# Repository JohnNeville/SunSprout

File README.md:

# SunSprout

> [!WARNING]
> **Prototype hardware: charging works, validation is incomplete.** A first hub was built and
> tested from commit [`1645733`](https://github.com/JohnNeville/SunSprout/commit/1645733).
> Charging, charge termination and running from the battery alone worked on it, and testing also
> found issues. The current design files fix them, but that revision has **not been built yet**,
> and not every feature has been bench-tested. [Testing status](https://johnneville.github.io/SunSprout/docs/testing-status)
> lists each feature. You can build the tested prototype with its known issues, or the current
> design with its untested fixes. The commit history shows what changed.
>
> **Before you connect a battery:**
> - **Set the cell chemistry in the firmware first.** The charger comes up for a 4.2 V cell by
>   default. The firmware sets the charge limit from `cell_chemistry` (LiFePO4 charges to 3.65 V),
>   so set it to match your cell.
> - **Fit a 10 kΩ NTC thermistor** on the battery, or set `ts_ignore: true` (turns temperature
>   protection off). Otherwise the charger won't charge.
> - **Set the charge current in the firmware to suit your pack, and never above 2000 mA.** The
>   hardware input-current limit only restricts it loosely, so the firmware ceiling is what holds it.
> - **Check polarity.** The reverse-polarity protection was changed after the prototype and the
>   new design is untested on hardware.
>
> A wrongly configured charger can damage a lithium cell. Build one board and bring it up on USB
> power with no battery before ordering a batch.
>
> Feedback is welcome, especially on the power path, the charger and fuel-gauge configuration, and
> anything in [docs/hub/modules/](docs/hub/modules/) where the reasoning looks wrong.

An open-hardware solar and battery powered sensor system. SunSprout covers both halves of a
deployment: the **hub**, a custom board that manages power and talks to the network, and the
**remote sensors** that connect back to it over a long cable run.

The hub is the custom hardware in this project. The remote sensors are largely assembled from
existing modules, and are documented here so that a whole system can be reproduced rather than
inferred.

## The hub

A compact power-management and connectivity board built around the **ESP32-C5**. It takes power
from USB-C, a small DC or solar source, or a lithium battery. It charges the battery, regulates
a 3.3 V system rail, and exposes two independent I2C buses — one for its own power-management
ICs, and one for sensors, buffered onto a differential pair so it can drive a long cable.

| | |
|---|---|
| Documentation site | **[johnneville.github.io/SunSprout](https://johnneville.github.io/SunSprout/)** — pinout, connectors, power behaviour |
| Build one | [Order from JLCPCB](website/docs/fabrication/ordering-jlcpcb.md) and [Getting started](website/docs/getting-started.md) — fabrication settings, assembly checks, first flash |
| Design files | [hardware/hub/](hardware/hub/) — KiCad 10 project, hand-routed |
| Why it is built this way | [docs/hub/modules/](docs/hub/modules/) — per-IC design notes |
| Firmware | [SunSprout-firmware](https://github.com/JohnNeville/SunSprout-firmware) — ESPHome configuration; [docs/hub/firmware.md](docs/hub/firmware.md) for the reasoning |
| Off-board parts you need | [docs/hub/extra-components.md](docs/hub/extra-components.md) |

Every IC's datasheet-required external components are drawn directly into the schematic rather
than treated as black-box breakout modules. The schematic and PCB are maintained by hand in
KiCad; there is no generator producing them.

### Design decisions worth knowing up front

- **Two independent I2C buses.** An always-on internal bus carries the charger and the fuel
  gauge. A separate switched bus feeds the differential buffer that drives the two 8P8C jacks,
  plus its own STEMMA QT connector. A fault on a long external cable cannot stall the bus that
  reports the battery state.
- **Protection sized to what each port is for.** ESD/TVS on the ports meant to carry a cable
  off-board — the differential I2C lines on the 8P8C jacks, the USB-C data lines, and the USB
  `VBUS` rail. The STEMMA QT ports, GPIO headers and thermistor inputs have none, by design:
  they are for sensors inside the same enclosure. Reverse-polarity protection guards the
  battery and solar inputs, each sized to that input's real voltage range; USB-C gets none,
  being a keyed, spec-defined connector that cannot be connected backwards.
- **Alert lines go to their own GPIOs.** The charger and the fuel gauge each get a dedicated
  interrupt pin, so firmware reacts to a fault without polling, and without interrogating both
  devices to find which one raised it.
- **Connector families differ by role on purpose.** The battery and solar inputs use physically
  different connectors, so a solar source cannot be plugged into the battery input. The two
  thermistor inputs are a third family again, chosen to be field-terminable rather than
  requiring a pre-terminated probe.

## Remote sensors

A custom board, `SunSproutSatellite` ([hardware/satellite/](hardware/satellite/)), is the
differential-I2C endpoint that sits at the plant end of the cable — it terminates the line,
converts back to standard I2C, and reads four capacitive soil-moisture probes plus one
1-Wire soil-temperature probe. It integrates what was previously an off-the-shelf SparkFun
QwiicBus EndPoint wired to a breadboarded ADS1115. See
[docs/satellite/modules/](docs/satellite/modules/) for the per-IC design notes, and
[Use Cases](https://johnneville.github.io/SunSprout/use-cases) for the deployed topology.

**Status: schematic-capture spec only** — the KiCad project is scaffolded but no board has
been fabricated yet.

## Repository layout

```
.
├── hardware/
│   ├── hub/                  # the hub's KiCad project, libraries, and SPICE decks
│   └── satellite/            # the satellite's KiCad project and libraries
├── firmware/                 # ESPHome configuration for the hub
├── docs/
│   ├── hub/
│   │   ├── modules/          # per-IC design notes: part choice, passive values, constraints
│   │   ├── firmware.md       # why the firmware is configured the way it is
│   │   └── extra-components.md
│   └── satellite/
│       └── modules/          # per-IC design notes for the satellite board
├── tools/                    # Dockerised KiCad CLI: validation, fab outputs, doc assets
└── website/                  # Docusaurus documentation site
```

## Documentation

The prose documentation is split by audience:

- **[docs/hub/modules/](docs/hub/modules/)** explains *why* the hub is built the way it is —
  why each part was chosen, and why its passives have the values and packages they do. Written
  for someone reading the design cold. Start at the [index](docs/hub/modules/README.md).
- **[docs/hub/firmware.md](docs/hub/firmware.md)** explains the firmware decisions — why the
  watchdog is off, why the charge voltage comes from the declared chemistry, and what the
  `SFET_PRESENT` bit unlocks. The configuration itself is in [SunSprout-firmware](https://github.com/JohnNeville/SunSprout-firmware); the chip
  drivers live in [esphome-bq-drivers](https://github.com/JohnNeville/esphome-bq-drivers).
- **[website/](website/)** is the source for the user-facing documentation site, published at
  **[johnneville.github.io/SunSprout](https://johnneville.github.io/SunSprout/)**: pinout,
  connectors, power behaviour, and downloads.

Manufacturer datasheets are deliberately not redistributed here. Each design note names the
exact part number, so you can get the datasheet from the manufacturer.

## Building and validating

Docker is the only prerequisite. No local KiCad installation is required.

```bash
tools/run_kicad_validation.sh
```

```bash
tools/generate-docs-assets.sh
```

The first runs ERC and DRC. The second regenerates the board renders, schematic PDF, STEP
model, interactive BOM, and pinout diagram under `website/static/`. Re-run it after any
schematic or layout change, so that the published assets never go stale.

See [hardware/hub/README.md](hardware/hub/README.md) for what you can do with the KiCad project
without any extra setup, and which external libraries are optional.

## License

Copyright John Neville 2026.
This source describes Open Hardware and is licensed under the CERN-OHL-S v2.

You may redistribute and modify this source and make products using it
under the terms of the CERN-OHL-S v2 (https://ohwr.org/cern_ohl_s_v2.txt).

This source is distributed WITHOUT ANY EXPRESS OR IMPLIED WARRANTY,
INCLUDING OF MERCHANTABILITY, SATISFACTORY QUALITY AND FITNESS FOR A
PARTICULAR PURPOSE. Please see the CERN-OHL-S v2 for applicable conditions.

Source location: https://github.com/JohnNeville/SunSprout

See [LICENSE](LICENSE) for the full license text.

This design also vendors Espressif's official CC BY-SA 4.0 KiCad library for the ESP32-C5
module. See [NOTICE.md](NOTICE.md) for that credit and an acknowledgment of other technical
references consulted during design.

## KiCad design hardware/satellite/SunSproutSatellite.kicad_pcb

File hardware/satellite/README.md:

# SunSproutSatellite — KiCad project

The satellite board's KiCad 10 project. Open `SunSproutSatellite.kicad_pro`.

This board is a differential-I2C endpoint: it terminates the far end of the cable coming
from a [SunSproutHub](../hub/), converts the differential pair back to standard I2C, and
reads four capacitive soil-moisture probes plus one 1-Wire soil-temperature probe. For the
design reasoning behind each part, see [docs/satellite/modules/](../../docs/satellite/modules/).

**Status: Complete 4-layer PCB layout.** The project schematic and PCB layout are fully completed, featuring a 4-layer stackup (JLC04161H-7628), controlled-impedance differential I2C routing, dedicated inner reference planes (`In1.Cu` and `In2.Cu`), ESD protection, cable power decoupling, and complete DFM rule verification with 0 DRC violations.

## Layout & Architecture

| Path | Contents |
|---|---|
| `SunSproutSatellite.kicad_sch` | Root hierarchical schematic |
| `sheets/i2c_endpoint_v1.kicad_sch` | Differential I2C endpoint, PCA9615 buffer, termination array, cable power entry, power status LED (LED1), cut jumper (JP19), and headers J1, J7, J8, J9 |
| `sheets/adc_sensors_v1.kicad_sch` | ADS1115 16-bit 4-channel ADC, JST PH moisture probe headers (J2–J5), and address jumper JP1 |
| `sheets/onewire_v1.kicad_sch` | DS2482S-100+ I2C to 1-Wire bridge, JST PH probe header (J6), and bit-weighted address jumper JP16 |
| `SunSproutSatellite.kicad_pcb` | Completed 4-layer PCB layout (27.25 mm × 51.10 mm) with inner ground/power planes |
| `SunSproutSatellite.kicad_dru` | Custom JLCPCB 4-layer design rules (clearances, trace widths, track angles, and annular rings) |
| `../libraries/` | Project-specific symbol & footprint library (shared with Hub) |

## External library dependencies

Two parts have no stock KiCad equivalent and are copied in from the hub's own libraries
rather than referenced externally:

| Part | Symbol | Footprint |
|---|---|---|
| PCA9615 differential I2C buffer | `project:PCA9615DPZ` | `Snapeda:TSSOP10_SOT552-1_NXP-L` |
| 8P8C/RJ45 jack | `project:RJHSE5380_QwiicBusCompatible` | `Snapeda:AMPHENOL_RJHSE5380` |

Both footprints resolve externally via `KICAD_3RD_PARTY` the same way the hub's do (see
[hardware/hub/README.md](../hub/README.md#external-library-dependencies)) — or, simpler for
a board with only two such parts: place each once, then use KiCad's "Update PCB from
Schematic" so the footprint geometry gets embedded directly into this project's own files,
exactly as the hub does for every part once placed. After that, no external dependency
remains for either part.

Every other part on this board — the ADS1115 ADC, the DS2482 1-Wire bridge, the ESD
protection diode array, and all connectors — resolves from KiCad's own stock libraries with
zero setup.

## Regenerating the documentation assets

Documentation assets (3D board renders, interactive BOM, and interactive pinout SVGs) are generated via `tools/generate-docs-assets.sh`. The generated assets live under `website/static/` and `website/static/img/`. Release assets (schematic PDFs, STEP models, and fabrication zips) are produced by the release workflow.

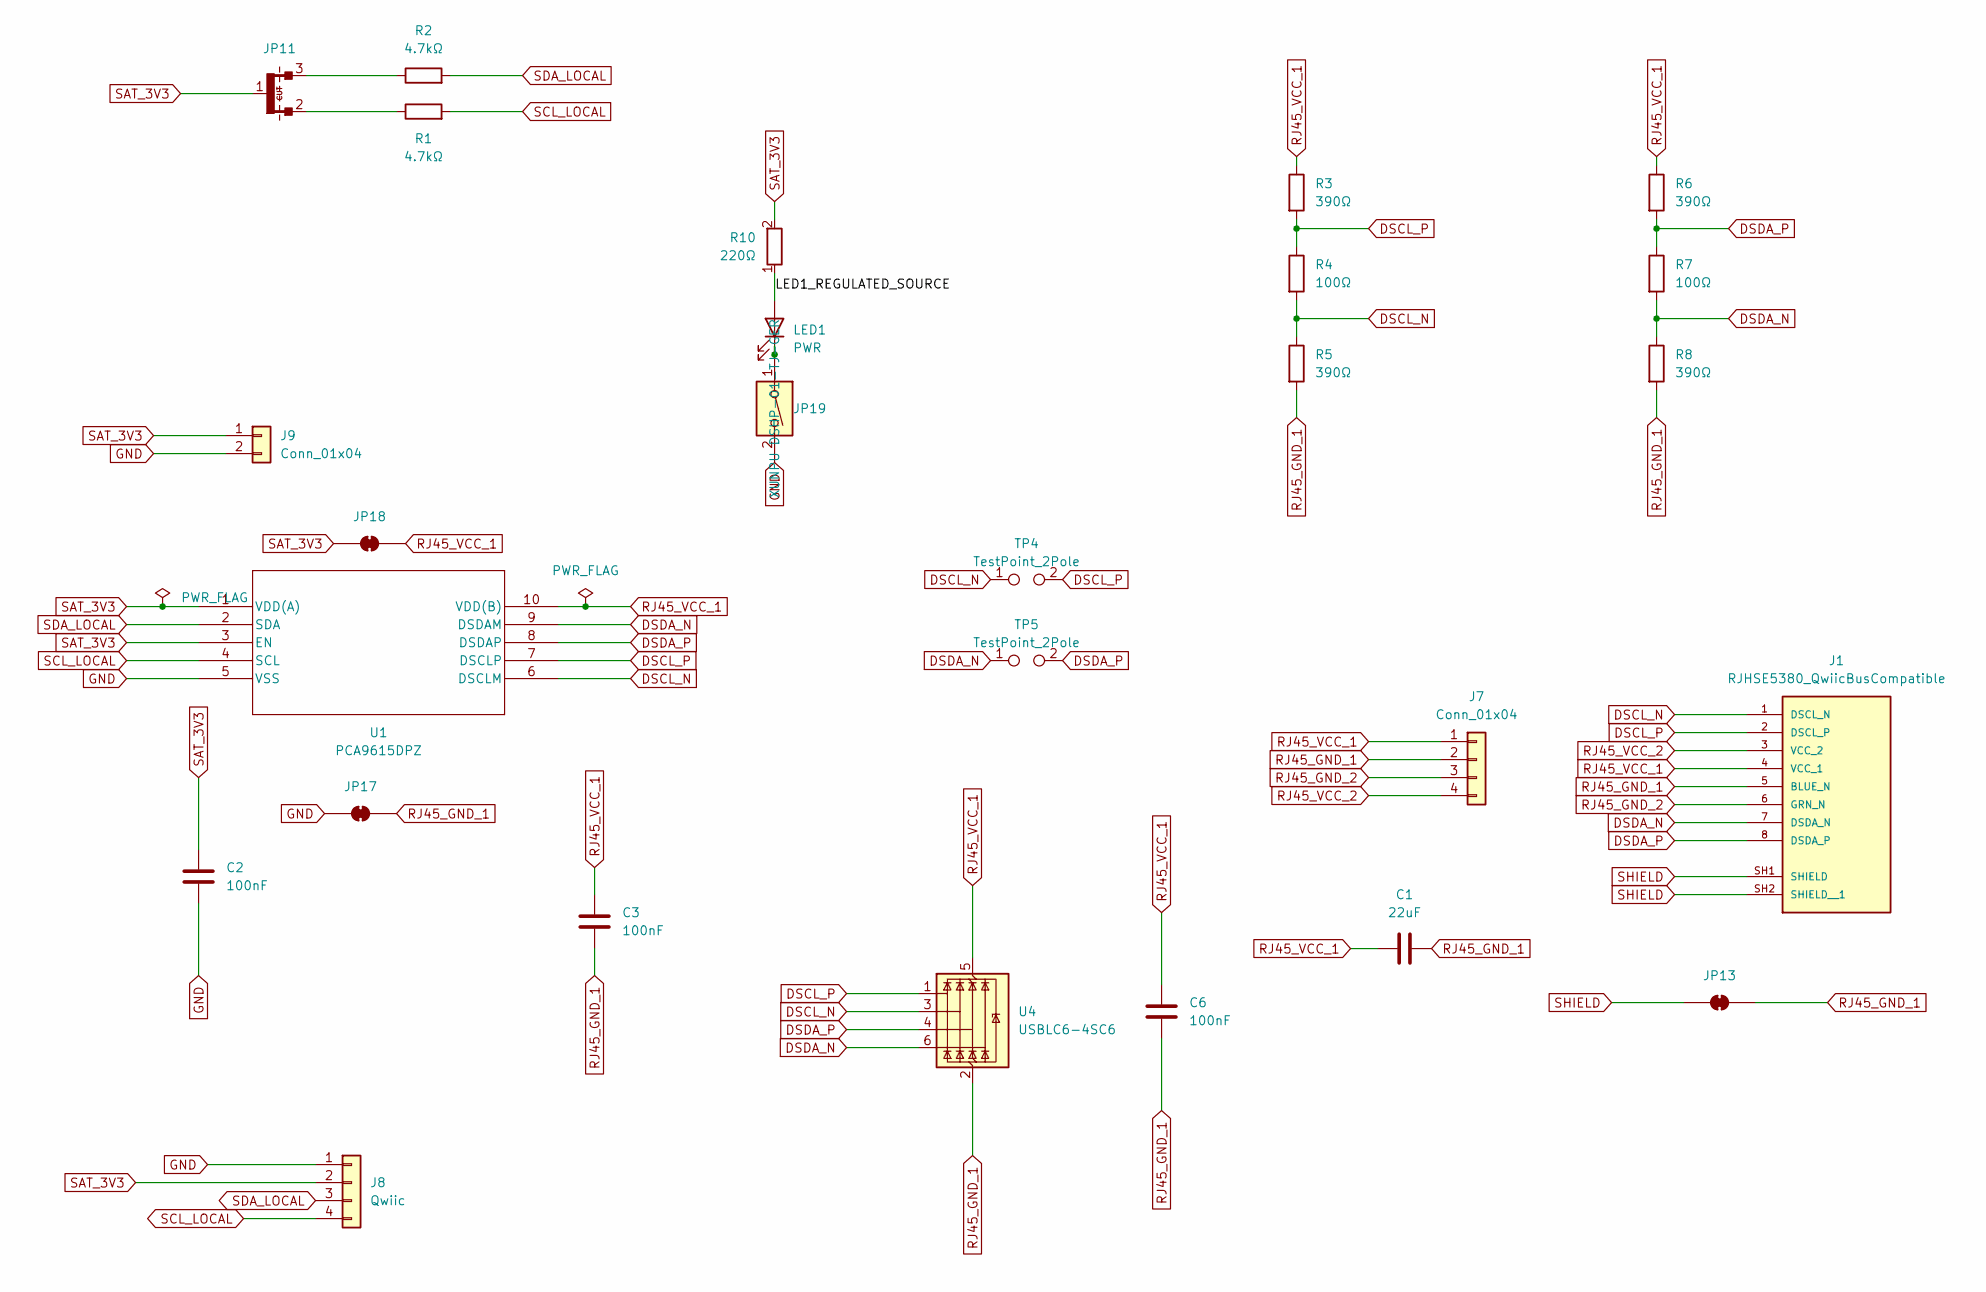
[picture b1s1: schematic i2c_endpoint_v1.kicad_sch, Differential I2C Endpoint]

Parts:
C1: 22uF; C_0805_2012Metric_Pad1.18x1.45mm_HandSolder; LCSC Part C45783
C2, C3, C6: 100nF; C_0805_2012Metric_Pad1.18x1.45mm_HandSolder; LCSC Part C28233
J1: RJHSE5380_QwiicBusCompatible; AMPHENOL_RJHSE5380; LCSC Part C464586
J7: Conn_01x04; PinHeader_1x04_P2.54mm_Vertical; LCSC Part C22368214
J8: Qwiic; JST_SH_BM04B-SRSS-TB_1x04-1MP_P1.00mm_Vertical; MPN BM04B-SRSS-TB(LF)(SN); LCSC Part C160390
J9: Conn_01x04; PinHeader_1x02_P2.54mm_Vertical; LCSC Part C22368214
JP11: SolderJumper_3_DualPullUp_Bridged; SolderJumper-3_P1.3mm_DualPullUp_SingleCut_RoundedPad1.0x1.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
JP13, JP17, JP18: SolderJumper_2_Bridged; SolderJumper-2_P1.3mm_Bridged_RoundedPad1.0x1.5mm
JP19: DIP_x01_1,27mm; SW_DIP_x1_XUNPU_DSHP-01-TJ-GER_Slide_JLead; LCSC Part C7471388
LED1: PWR; LED_0805_2012Metric_Pad1.15x1.40mm_HandSolder
R1, R2: 4.7kΩ; R_0805_2012Metric_Pad1.20x1.40mm_HandSolder; LCSC Part C17673
R3, R5, R6, R8: 390Ω; R_0805_2012Metric_Pad1.20x1.40mm_HandSolder; LCSC Part C17655
R4, R7: 100Ω; R_0805_2012Metric_Pad1.20x1.40mm_HandSolder; LCSC Part C17408
R10: 220Ω; R_0805_2012Metric_Pad1.20x1.40mm_HandSolder
TP4, TP5: TestPoint_2Pole; TestPoint_2Pole_Pad_D1.0mm
U1: PCA9615DPZ; TSSOP10_SOT552-1_NXP-Recommended; LCSC Part C3824272
U4: USBLC6-4SC6; SOT-23-6; LCSC Part C5180279

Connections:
/Differential I2C Endpoint/LED1_REGULATED_SOURCE: LED1.2 (A), R10.1
DSCL_N: J1.1 (DSCL_N), R4.2, R5.1, TP4.1, U1.6 (DSCLM), U4.3 (I/O2)
DSCL_P: J1.2 (DSCL_P), R3.2, R4.1, TP4.2, U1.7 (DSCLP), U4.1 (I/O1)
DSDA_N: J1.7 (DSDA_N), R7.2, R8.1, TP5.1, U1.9 (DSDAM), U4.6 (I/O4)
DSDA_P: J1.8 (DSDA_P), R6.2, R7.1, TP5.2, U1.8 (DSDAP), U4.4 (I/O3)
GND: C2.2, J8.1 (GND), J9.2, JP17.2 (B), JP19.2, U1.5 (VSS); also elsewhere on the board
unnamed: JP11.2 (SCL_PU), R1.1
unnamed: JP11.3 (SDA_PU), R2.1
unnamed: JP19.1, LED1.1 (K)
RJ45_GND_1: C1.2, C3.2, C6.2, J1.5 (BLUE_N), J7.2, JP13.2 (B), JP17.1 (A), R5.2, R8.2, U4.2 (GND)
RJ45_GND_2: J1.6 (GRN_N), J7.3
RJ45_VCC_1: C1.1, C3.1, C6.1, J1.4 (VCC_1), J7.1, JP18.1 (A), R3.1, R6.1, U1.10 (VDD(B)), U4.5 (VBUS)
RJ45_VCC_2: J1.3 (VCC_2), J7.4
SAT_3V3: C2.1, J8.2 (3v3), J9.1, JP11.1 (VCC), JP18.2 (B), R10.2, U1.1 (VDD(A)), U1.3 (EN); also elsewhere on the board
SCL_LOCAL: J8.4 (SCL), R1.2, U1.4 (SCL); also elsewhere on the board
SDA_LOCAL: J8.3 (SDA), R2.2, U1.2 (SDA); also elsewhere on the board
SHIELD: J1.SH1 (SHIELD), J1.SH2 (SHIELD__1), JP13.1 (A)

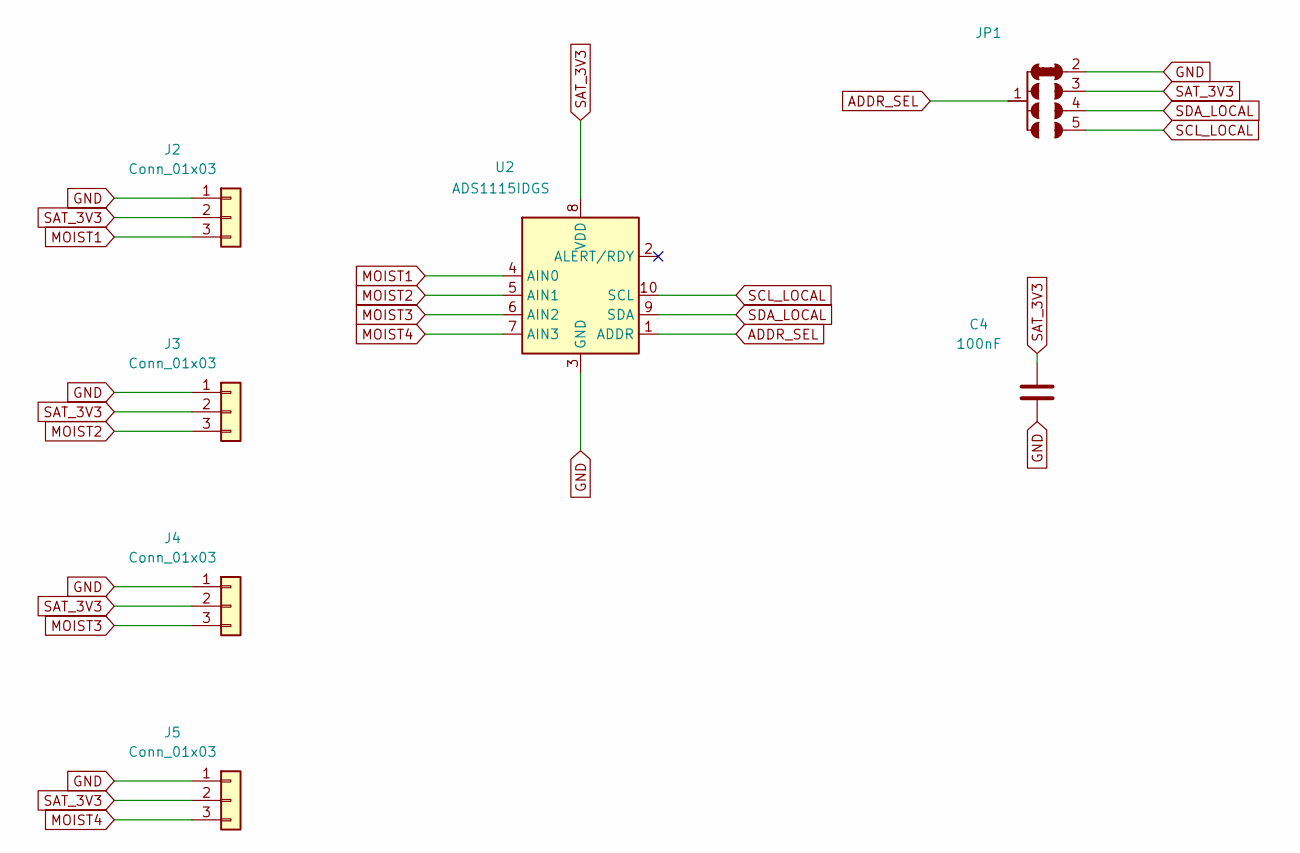
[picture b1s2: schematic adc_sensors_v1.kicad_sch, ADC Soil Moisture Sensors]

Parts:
C4: 100nF; C_0805_2012Metric_Pad1.18x1.45mm_HandSolder; LCSC Part C28233
J2, J3, J4, J5: Conn_01x03; JST_PH_B3B-PH-K_1x03_P2.00mm_Vertical; LCSC Part C131339
JP1: SolderJumper_4_Bridged12; ADCAddrJumper1mmPads
U2: ADS1115IDGS; TSSOP-10_3x3mm_P0.5mm; LCSC Part C37593

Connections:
ADDR_SEL: JP1.1 (ADDR), U2.1 (ADDR)
GND: C4.2, J2.1, J3.1, J4.1, J5.1, JP1.2 (0x48), U2.3 (GND); also elsewhere on the board
MOIST1: J2.3, U2.4 (AIN0)
MOIST2: J3.3, U2.5 (AIN1)
MOIST3: J4.3, U2.6 (AIN2)
MOIST4: J5.3, U2.7 (AIN3)
SAT_3V3: C4.1, J2.2, J3.2, J4.2, J5.2, JP1.3 (0x49), U2.8 (VDD); also elsewhere on the board
SCL_LOCAL: JP1.5 (0x4B), U2.10 (SCL); also elsewhere on the board
SDA_LOCAL: JP1.4 (0x4A), U2.9 (SDA); also elsewhere on the board

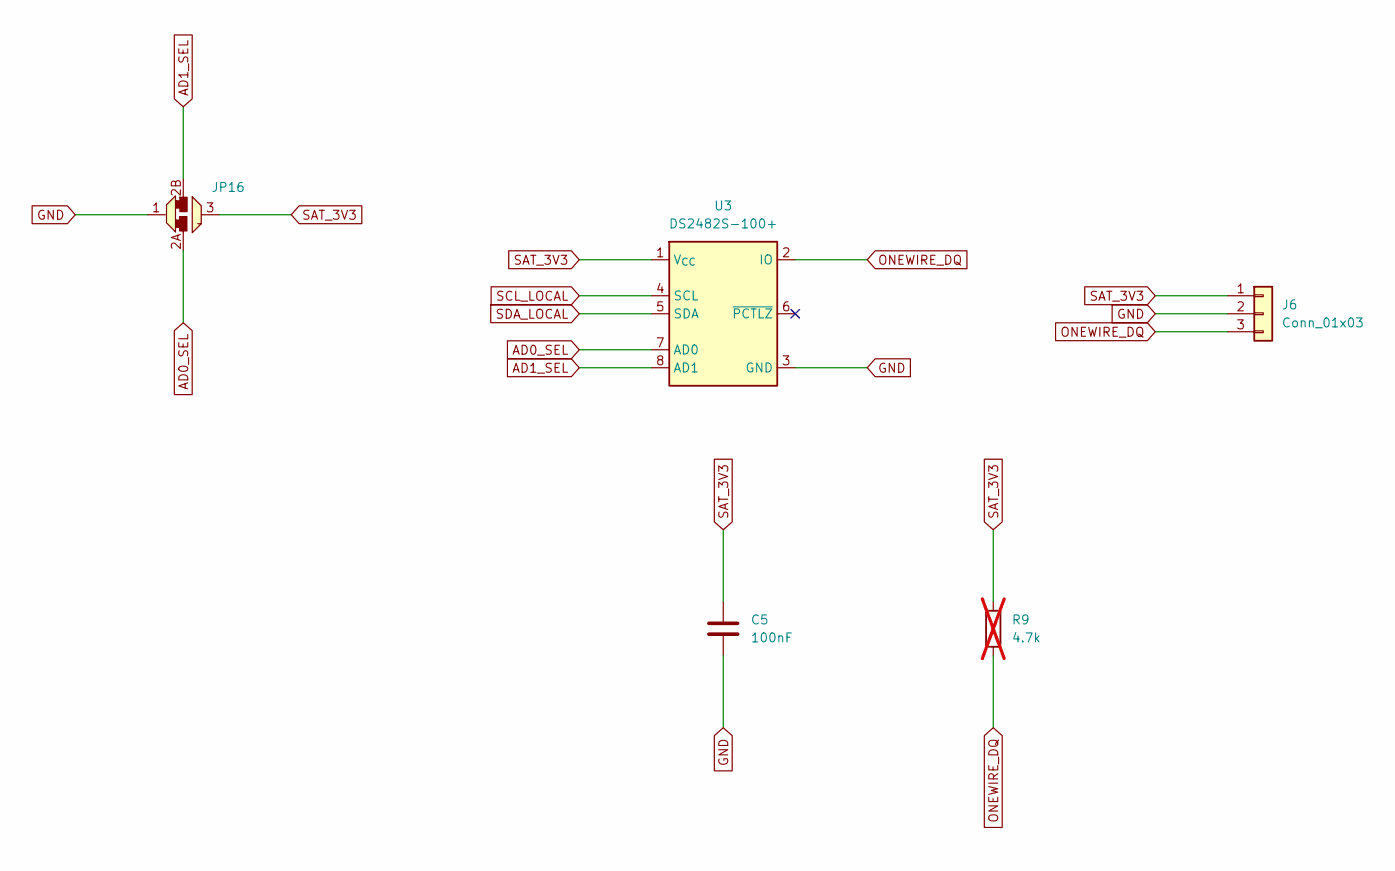
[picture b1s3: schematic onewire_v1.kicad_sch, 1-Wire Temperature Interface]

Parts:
C5: 100nF; C_0805_2012Metric_Pad1.18x1.45mm_HandSolder; LCSC Part C28233
J6: Conn_01x03; JST_PH_B3B-PH-K_1x03_P2.00mm_Vertical; LCSC Part C131339
JP16: Dual Solder Jumper with Both connected to Pin 1.; SolderJumper-3_P_1WAddr
R9: 4.7k; R_0805_2012Metric_Pad1.20x1.40mm_HandSolder; LCSC Part C23162; not fitted
U3: DS2482S-100+; SOIC-8_3.9x4.9mm_P1.27mm; LCSC Part C143306

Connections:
AD0_SEL: JP16.2A (C), U3.7 (AD0)
AD1_SEL: JP16.2B (C), U3.8 (AD1)
GND: C5.2, J6.2, JP16.1 (A), U3.3 (GND); also elsewhere on the board
ONEWIRE_DQ: J6.3, R9.2, U3.2 (IO)
SAT_3V3: C5.1, J6.1, JP16.3 (B), R9.1, U3.1 (V_{CC}); also elsewhere on the board
SCL_LOCAL: U3.4 (SCL); also elsewhere on the board
SDA_LOCAL: U3.5 (SDA); also elsewhere on the board

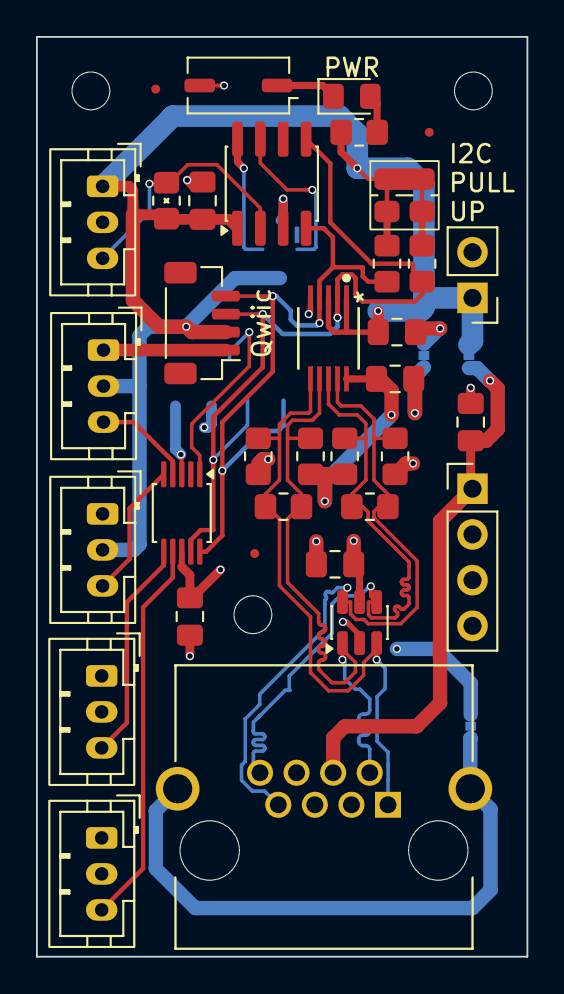
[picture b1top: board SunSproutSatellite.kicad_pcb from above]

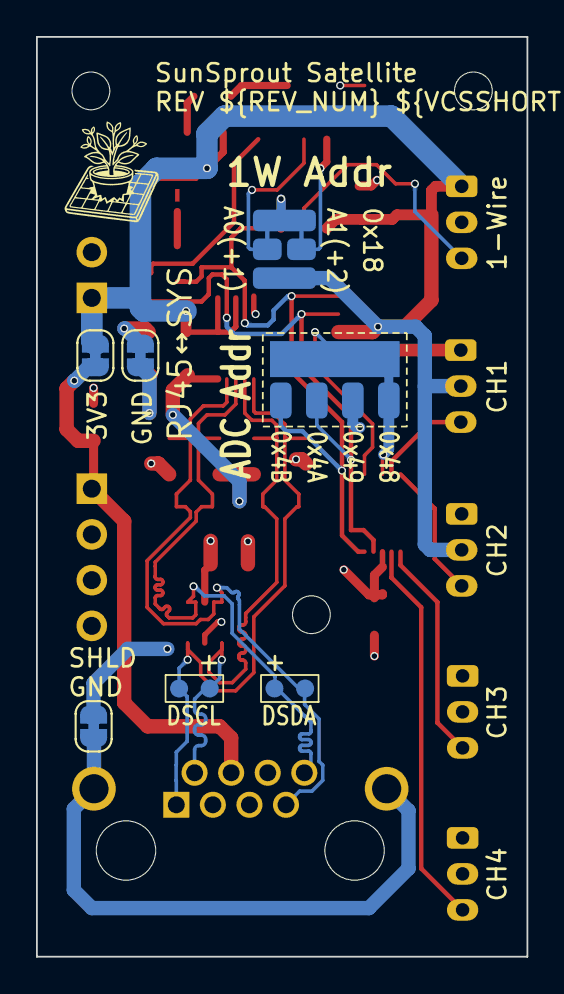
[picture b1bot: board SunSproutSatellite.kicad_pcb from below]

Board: 4 copper layers, 27.2 x 51.1 mm, 45 parts (7 on the bottom side), 25 nets.

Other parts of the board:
MP1, MP2, MP3: MountingHole_2.1mm
Ref**: Fiducial_0.5mm_Mask1mm
Ref**#2, Ref**#3: Fiducial_0.5mm_Mask1mm

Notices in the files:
hardware/hub/SunSproutHub.kicad_pcb:
Licensed under CERN-OHL-S v2
